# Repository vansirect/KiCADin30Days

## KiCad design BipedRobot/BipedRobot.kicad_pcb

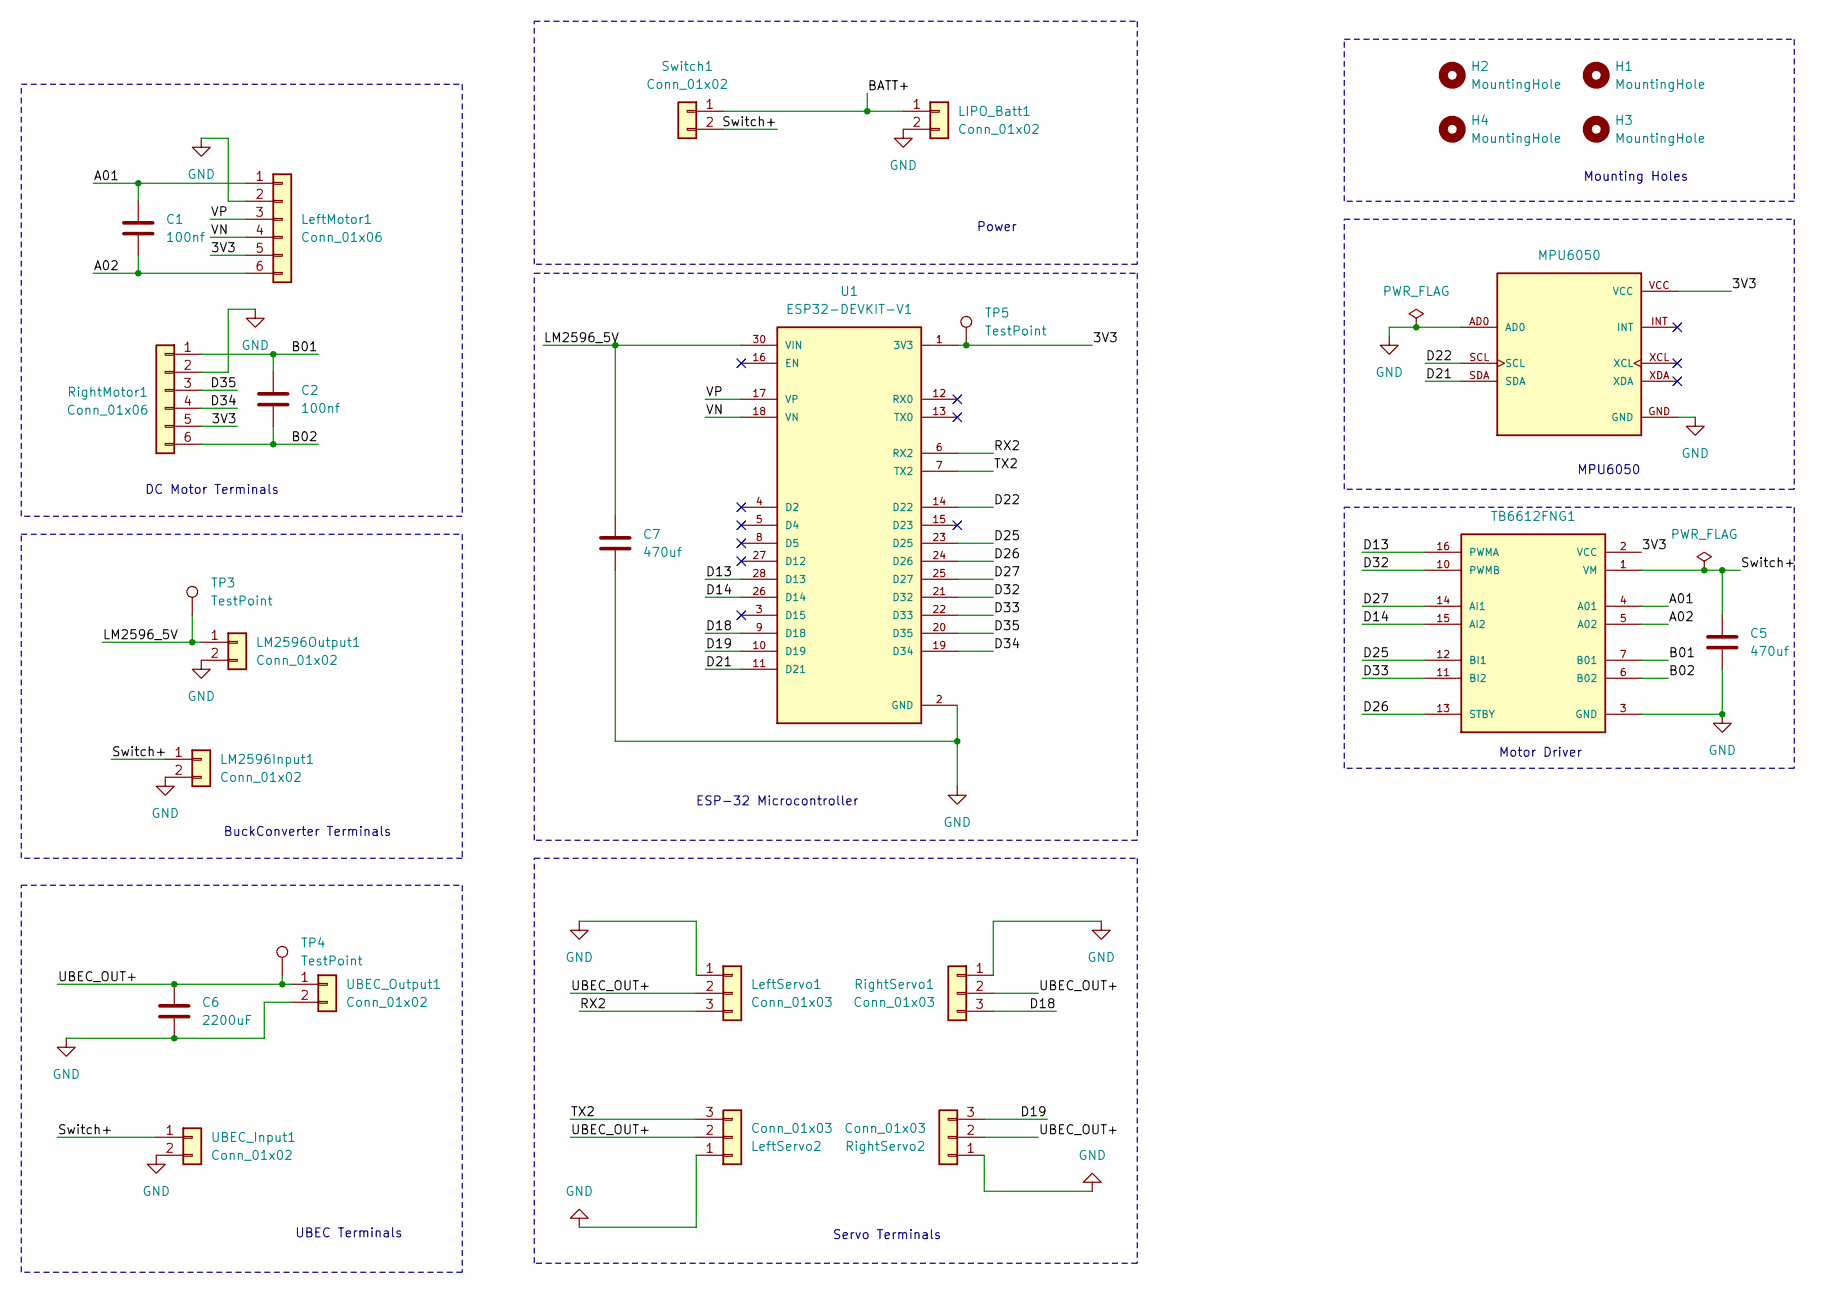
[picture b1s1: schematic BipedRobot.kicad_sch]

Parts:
C1, C2: 100nf; C_Disc_D5.0mm_W2.5mm_P5.00mm
C5, C7: 470uf; CP_Radial_D10.0mm_P5.00mm
C6: 2200uF; CP_Radial_D16.0mm_P7.50mm
H1, H2, H3, H4: MountingHole; MountingHole_3.2mm_M3
LIPO_Batt1: Conn_01x02; AMASS_XT30UPB-M_1x02_P5.0mm_Vertical
LM2596Input1, LM2596Output1: Conn_01x02; SolderWire-0.5sqmm_1x02_P4.6mm_D0.9mm_OD2.1mm
LeftMotor1: Conn_01x06; JST_XH_B6B-XH-A_1x06_P2.50mm_Vertical
LeftServo1, LeftServo2: Conn_01x03; PinHeader_1x03_P2.54mm_Vertical
MPU6050: MPU6050; MODULE_OC09600; PARTREV NA
RightMotor1: Conn_01x06; JST_XH_B6B-XH-A_1x06_P2.50mm_Vertical
RightServo1, RightServo2: Conn_01x03; PinHeader_1x03_P2.54mm_Vertical
Switch1: Conn_01x02; SolderWire-0.5sqmm_1x02_P4.6mm_D0.9mm_OD2.1mm
TB6612FNG1: ROB-14450; MODULE_ROB-14450; PARTREV 11-13-17
TP3, TP4, TP5: TestPoint; TestPoint_Pad_D2.0mm
U1: ESP32-DEVKIT-V1; MODULE_ESP32_DEVKIT_V1; PARTREV N/A
UBEC_Input1: Conn_01x02; SolderWire-1sqmm_1x02_P5.4mm_D1.4mm_OD2.7mm
UBEC_Output1: Conn_01x02; SolderWire-1sqmm_1x02_P5.4mm_D1.4mm_OD2.7mm

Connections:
/3V3: LeftMotor1.5, MPU6050.VCC, RightMotor1.5, TB6612FNG1.2 (VCC), TP5.1 (1_1), U1.1 (3V3); also elsewhere on the board
/A01: C1.1, LeftMotor1.1, TB6612FNG1.4 (A01)
/A02: C1.2, LeftMotor1.6, TB6612FNG1.5 (A02)
/B01: C2.1, RightMotor1.1, TB6612FNG1.7 (B01)
/B02: C2.2, RightMotor1.6, TB6612FNG1.6 (B02)
/BATT+: LIPO_Batt1.1, Switch1.1
/D13: TB6612FNG1.16 (PWMA), U1.28 (D13); also elsewhere on the board
/D14: TB6612FNG1.15 (AI2), U1.26 (D14); also elsewhere on the board
/D18: RightServo1.3, U1.9 (D18); also elsewhere on the board
/D19: RightServo2.3, U1.10 (D19); also elsewhere on the board
/D21: MPU6050.SDA, U1.11 (D21); also elsewhere on the board
/D22: MPU6050.SCL, U1.14 (D22); also elsewhere on the board
/D25: TB6612FNG1.12 (BI1), U1.23 (D25); also elsewhere on the board
/D26: TB6612FNG1.13 (STBY), U1.24 (D26); also elsewhere on the board
/D27: TB6612FNG1.14 (AI1), U1.25 (D27); also elsewhere on the board
/D32: TB6612FNG1.10 (PWMB), U1.21 (D32); also elsewhere on the board
/D33: TB6612FNG1.11 (BI2), U1.22 (D33); also elsewhere on the board
/D34: RightMotor1.4, U1.19 (D34); also elsewhere on the board
/D35: RightMotor1.3, U1.20 (D35); also elsewhere on the board
/LM2596_5V: C7.1, LM2596Output1.1, TP3.1 (1_1), U1.30 (VIN); also elsewhere on the board
/RX2: LeftServo1.3, U1.6 (RX2); also elsewhere on the board
/Switch+: C5.1, LM2596Input1.1, Switch1.2, TB6612FNG1.1 (VM), UBEC_Input1.1
/TX2: LeftServo2.3, U1.7 (TX2); also elsewhere on the board
/UBEC_OUT+: C6.1, LeftServo1.2, LeftServo2.2, RightServo1.2, RightServo2.2, TP4.1 (1_1), UBEC_Output1.1
/VN: LeftMotor1.4, U1.18 (VN); also elsewhere on the board
/VP: LeftMotor1.3, U1.17 (VP); also elsewhere on the board
GND: C5.2, C6.2, C7.2, LIPO_Batt1.2, LM2596Input1.2, LM2596Output1.2, LeftMotor1.2, LeftServo1.1, LeftServo2.1, MPU6050.AD0, MPU6050.GND, RightMotor1.2, RightServo1.1, RightServo2.1, TB6612FNG1.3 (GND), TB6612FNG1.8 (GND), TB6612FNG1.9 (GND), U1.2 (GND), U1.29 (GND), UBEC_Input1.2, UBEC_Output1.2; also elsewhere on the board

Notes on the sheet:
DC Motor Terminals
MPU6050
Mounting Holes
Servo Terminals
Power
ESP-32 Microcontroller
UBEC Terminals
BuckConverter Terminals
Motor Driver

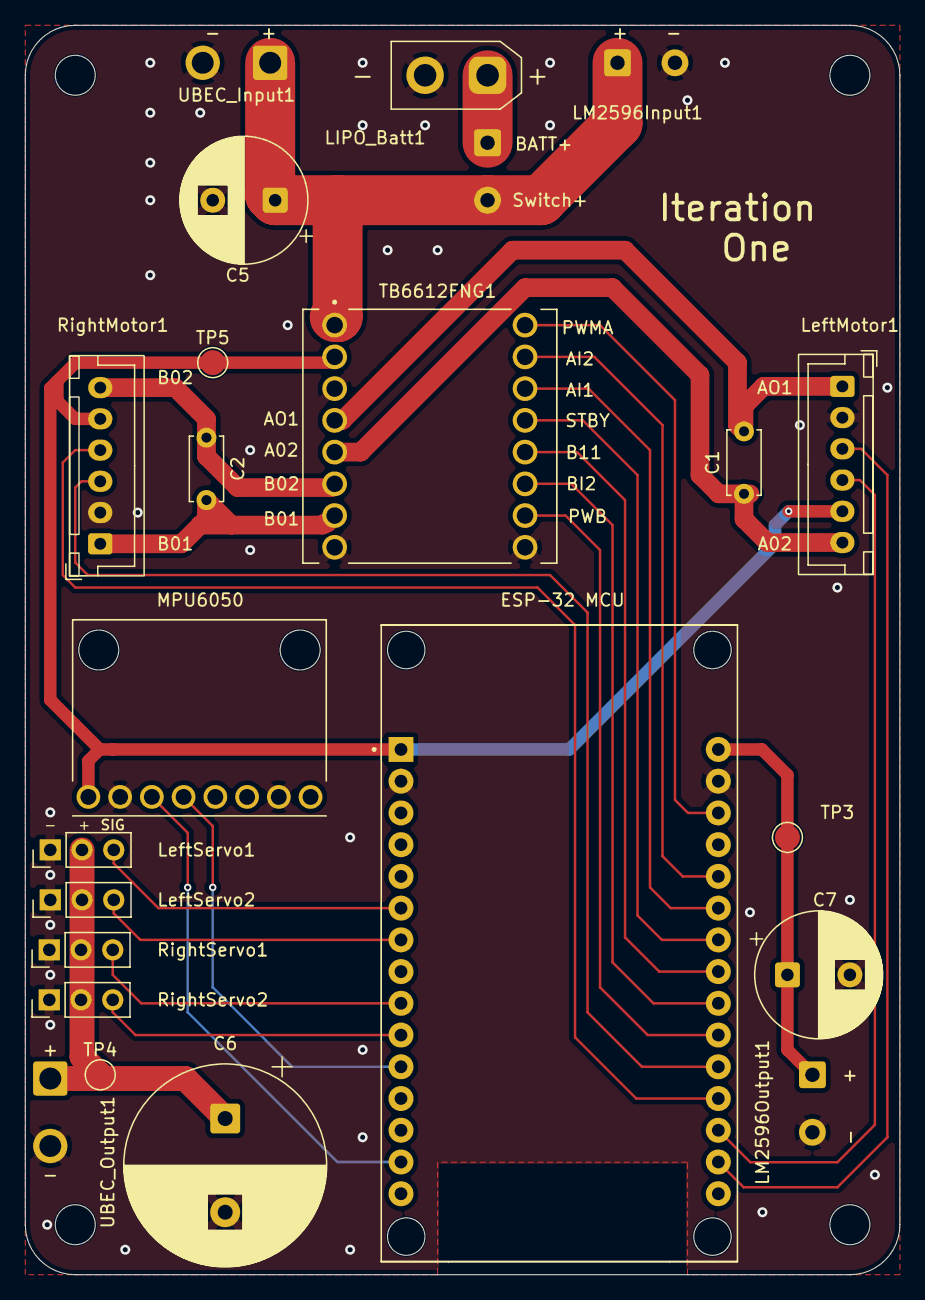
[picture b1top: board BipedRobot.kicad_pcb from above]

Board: 2 copper layers, 70.0 x 100.0 mm, 27 parts (0 on the bottom side), 27 nets.

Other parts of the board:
ESP-32 MCU: ESP32-DEVKIT-V1; MODULE_ESP32_DEVKIT_V1

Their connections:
/3V3: ESP-32 MCU.1 (3V3); also elsewhere on the board
/D13: ESP-32 MCU.28 (D13); also elsewhere on the board
/D14: ESP-32 MCU.26 (D14); also elsewhere on the board
/D18: ESP-32 MCU.9 (D18); also elsewhere on the board
/D19: ESP-32 MCU.10 (D19); also elsewhere on the board
/D21: ESP-32 MCU.11 (D21); also elsewhere on the board
/D22: ESP-32 MCU.14 (D22); also elsewhere on the board
/D25: ESP-32 MCU.23 (D25); also elsewhere on the board
/D26: ESP-32 MCU.24 (D26); also elsewhere on the board
/D27: ESP-32 MCU.25 (D27); also elsewhere on the board
/D32: ESP-32 MCU.21 (D32); also elsewhere on the board
/D33: ESP-32 MCU.22 (D33); also elsewhere on the board
/D34: ESP-32 MCU.19 (D34); also elsewhere on the board
/D35: ESP-32 MCU.20 (D35); also elsewhere on the board
/LM2596_5V: ESP-32 MCU.30 (VIN); also elsewhere on the board
/RX2: ESP-32 MCU.6 (RX2); also elsewhere on the board
/TX2: ESP-32 MCU.7 (TX2); also elsewhere on the board
/VN: ESP-32 MCU.18 (VN); also elsewhere on the board
/VP: ESP-32 MCU.17 (VP); also elsewhere on the board
GND: ESP-32 MCU.2 (GND), ESP-32 MCU.29 (GND); also elsewhere on the board

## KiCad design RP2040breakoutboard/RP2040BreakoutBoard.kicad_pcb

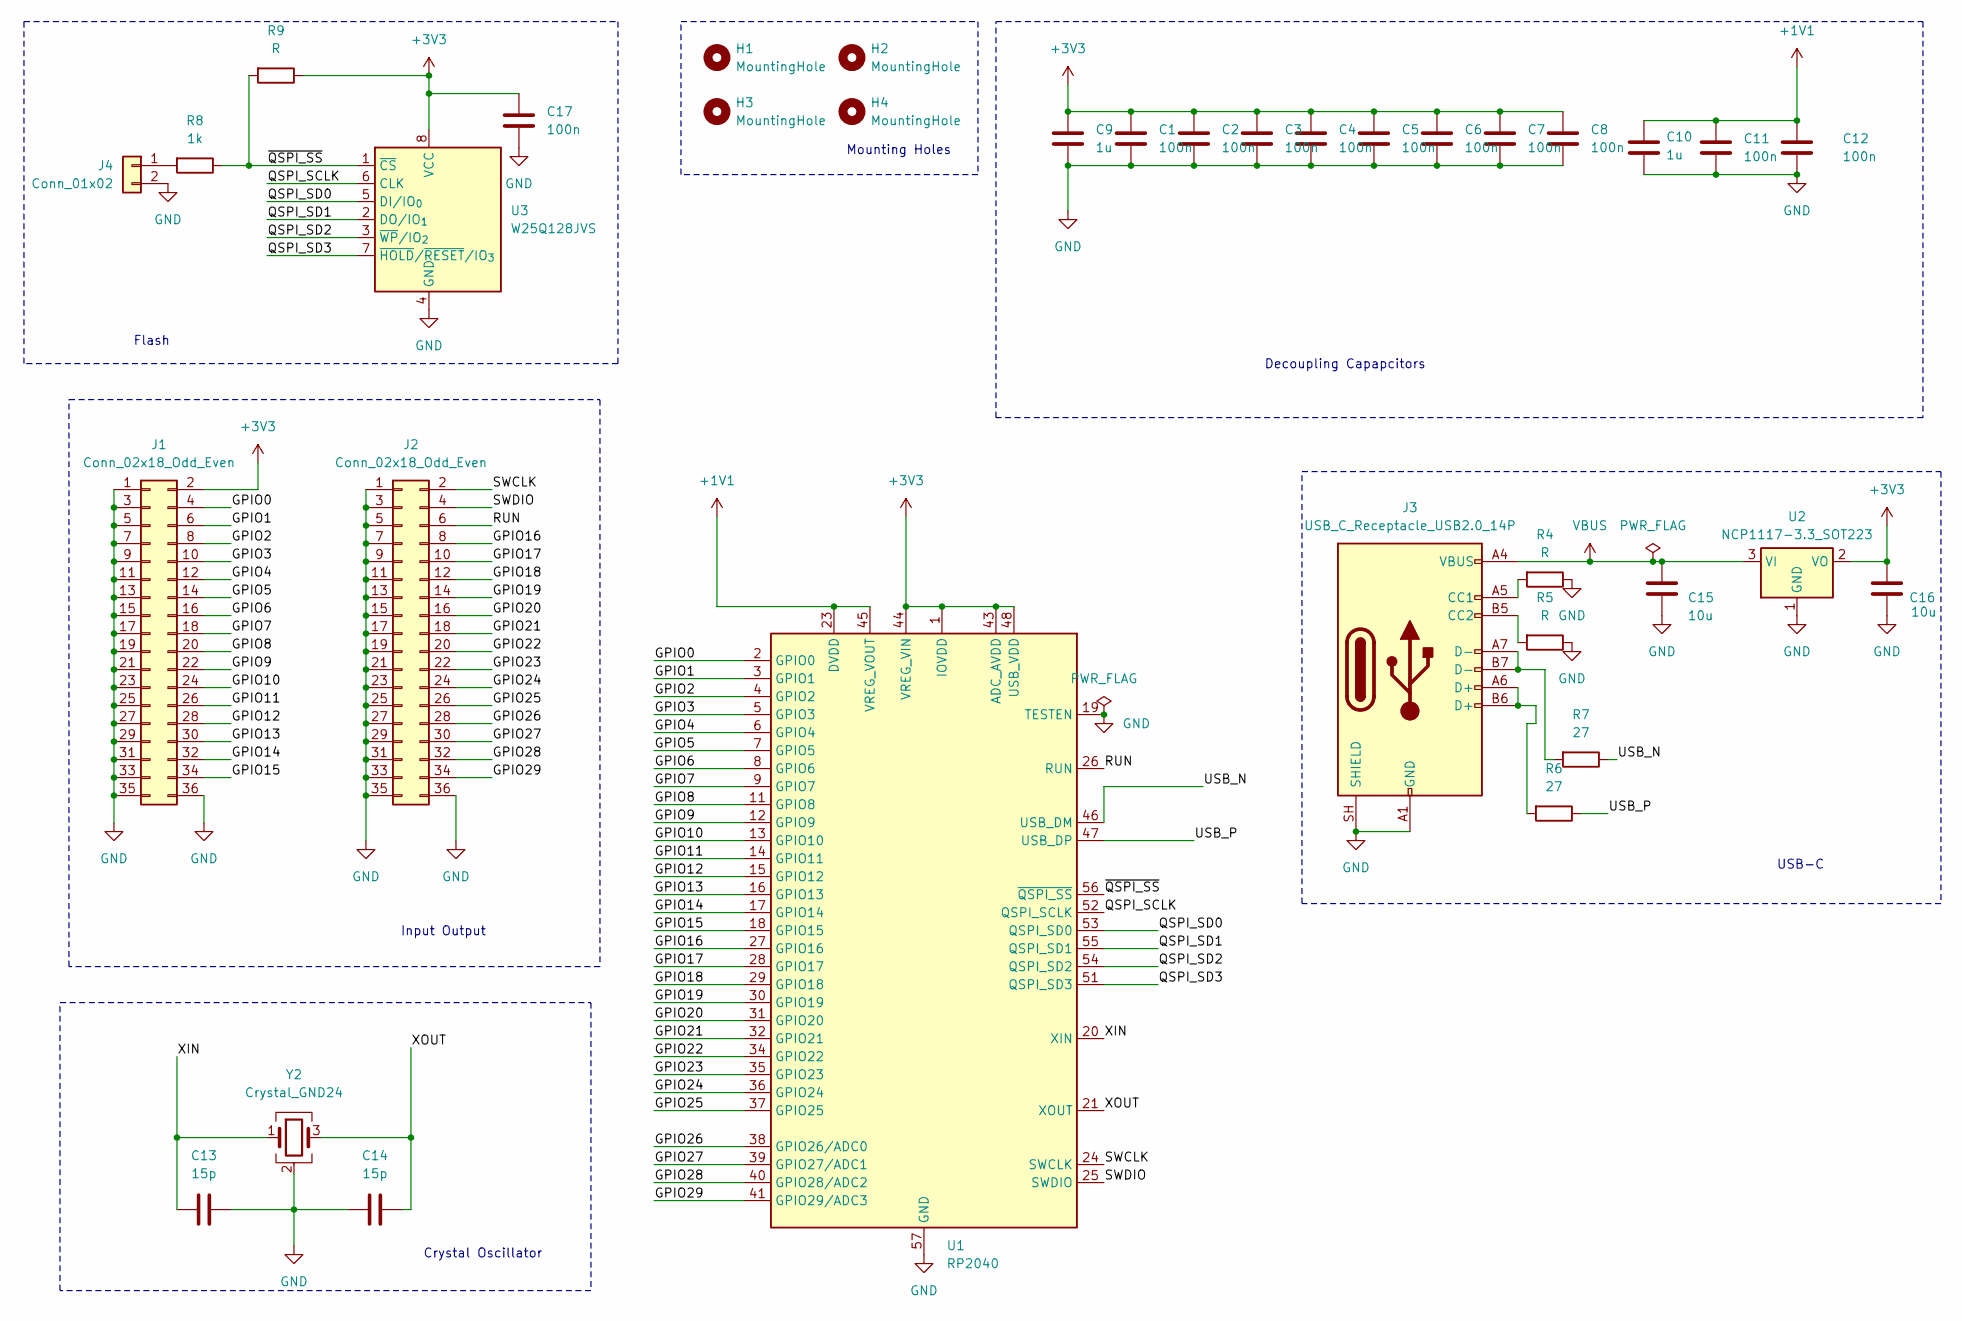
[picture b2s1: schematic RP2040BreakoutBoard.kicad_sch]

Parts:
C1, C2, C3, C4, C5, C6, C7, C8, C11, C12, C17: 100n; C_0603_1608Metric
C9, C10: 1u; C_0603_1608Metric
C13, C14: 15p; C_0603_1608Metric
C15, C16: 10u; C_0805_2012Metric
H1, H2, H3, H4: MountingHole; MountingHole_3.2mm_M3
J1, J2: Conn_02x18_Odd_Even; PinHeader_2x18_P2.54mm_Vertical
J3: USB_C_Receptacle_USB2.0_14P; USB_C_Receptacle_GCT_USB4105-xx-A_16P_TopMnt_Horizontal
J4: Conn_01x02; PinHeader_1x02_P2.54mm_Vertical
R4, R5, R9: R; R_0603_1608Metric
R6, R7: 27; R_0603_1608Metric
R8: 1k; R_0603_1608Metric
U1: RP2040; QFN-56-1EP_7x7mm_P0.4mm_EP3.2x3.2mm
U2: NCP1117-3.3_SOT223; SOT-223-3_TabPin2
U3: W25Q128JVS; SOIC-8_5.3x5.3mm_P1.27mm
Y2: Crystal_GND24; Crystal_SMD_3225-4Pin_3.2x2.5mm

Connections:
+1V1: C10.1, C11.1, C12.1, U1.23 (DVDD), U1.45 (VREG_VOUT), U1.50 (DVDD)
+3V3: C1.1, C2.1, C3.1, C4.1, C5.1, C6.1, C7.1, C8.1, C9.1, C16.2, C17.1, J1.2, R9.1, U1.1 (IOVDD), U1.10 (IOVDD), U1.22 (IOVDD), U1.33 (IOVDD), U1.42 (IOVDD), U1.43 (ADC_AVDD), U1.44 (VREG_VIN), U1.48 (USB_VDD), U1.49 (IOVDD), U2.2 (VO), U3.8 (VCC)
/GPIO0: J1.4, U1.2 (GPIO0)
/GPIO1: J1.6, U1.3 (GPIO1)
/GPIO2: J1.8, U1.4 (GPIO2)
/GPIO3: J1.10, U1.5 (GPIO3)
/GPIO4: J1.12, U1.6 (GPIO4)
/GPIO5: J1.14, U1.7 (GPIO5)
/GPIO6: J1.16, U1.8 (GPIO6)
/GPIO7: J1.18, U1.9 (GPIO7)
/GPIO8: J1.20, U1.11 (GPIO8)
/GPIO9: J1.22, U1.12 (GPIO9)
/GPIO10: J1.24, U1.13 (GPIO10)
/GPIO11: J1.26, U1.14 (GPIO11)
/GPIO12: J1.28, U1.15 (GPIO12)
/GPIO13: J1.30, U1.16 (GPIO13)
/GPIO14: J1.32, U1.17 (GPIO14)
/GPIO15: J1.34, U1.18 (GPIO15)
/GPIO16: J2.8, U1.27 (GPIO16)
/GPIO17: J2.10, U1.28 (GPIO17)
/GPIO18: J2.12, U1.29 (GPIO18)
/GPIO19: J2.14, U1.30 (GPIO19)
/GPIO20: J2.16, U1.31 (GPIO20)
/GPIO21: J2.18, U1.32 (GPIO21)
/GPIO22: J2.20, U1.34 (GPIO22)
/GPIO23: J2.22, U1.35 (GPIO23)
/GPIO24: J2.24, U1.36 (GPIO24)
/GPIO25: J2.26, U1.37 (GPIO25)
/GPIO26: J2.28, U1.38 (GPIO26/ADC0)
/GPIO27: J2.30, U1.39 (GPIO27/ADC1)
/GPIO28: J2.32, U1.40 (GPIO28/ADC2)
/GPIO29: J2.34, U1.41 (GPIO29/ADC3)
/QSPI_SCLK: U1.52 (QSPI_SCLK), U3.6 (CLK)
/QSPI_SD0: U1.53 (QSPI_SD0), U3.5 (DI/IO_{0})
/QSPI_SD1: U1.55 (QSPI_SD1), U3.2 (DO/IO_{1})
/QSPI_SD2: U1.54 (QSPI_SD2), U3.3 (~WP/IO_{2})
/QSPI_SD3: U1.51 (QSPI_SD3), U3.7 (~HOLD/~RESET/IO_{3})
/RUN: J2.6, U1.26 (RUN)
/SWCLK: J2.2, U1.24 (SWCLK)
/SWDIO: J2.4, U1.25 (SWDIO)
/USB_N: R7.1, U1.46 (USB_DM)
/USB_P: R6.1, U1.47 (USB_DP)
/XIN: C13.2, U1.20 (XIN), Y2.1
/XOUT: C14.1, U1.21 (XOUT), Y2.3
/~QSPI_SS: R8.1, R9.2, U1.56 (~QSPI_SS), U3.1 (~CS)
GND: C1.2, C2.2, C3.2, C4.2, C5.2, C6.2, C7.2, C8.2, C9.2, C10.2, C11.2, C12.2, C13.1, C14.2, C15.1, C16.1, C17.2, J1.1, J1.3, J1.5, J1.7, J1.9, J1.11, J1.13, J1.15, J1.17, J1.19, J1.21, J1.23, J1.25, J1.27, J1.29, J1.31, J1.33, J1.35, J1.36, J2.1, J2.3, J2.5, J2.7, J2.9, J2.11, J2.13, J2.15, J2.17, J2.19, J2.21, J2.23, J2.25, J2.27, J2.29, J2.31, J2.33, J2.35, J2.36, J3.A1 (GND), J3.A12 (GND), J3.B1 (GND), J3.B12 (GND), J3.SH (SHIELD), J4.2, R4.1, R5.1, U1.19 (TESTEN), U1.57 (GND), U2.1 (GND), U3.4 (GND), Y2.2 (G), Y2.4 (G)
unnamed: J3.A5 (CC1), R4.2
unnamed: J3.B5 (CC2), R5.2
unnamed: J3.A6 (D+), J3.B6 (D+), R6.2
unnamed: J3.A7 (D-), J3.B7 (D-), R7.2
unnamed: J4.1, R8.2
VBUS: C15.2, J3.A4 (VBUS), J3.A9 (VBUS), J3.B4 (VBUS), J3.B9 (VBUS), U2.3 (VI)

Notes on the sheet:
USB-C
Crystal Oscillator
Mounting Holes
Flash
Decoupling Capapcitors
Input Output

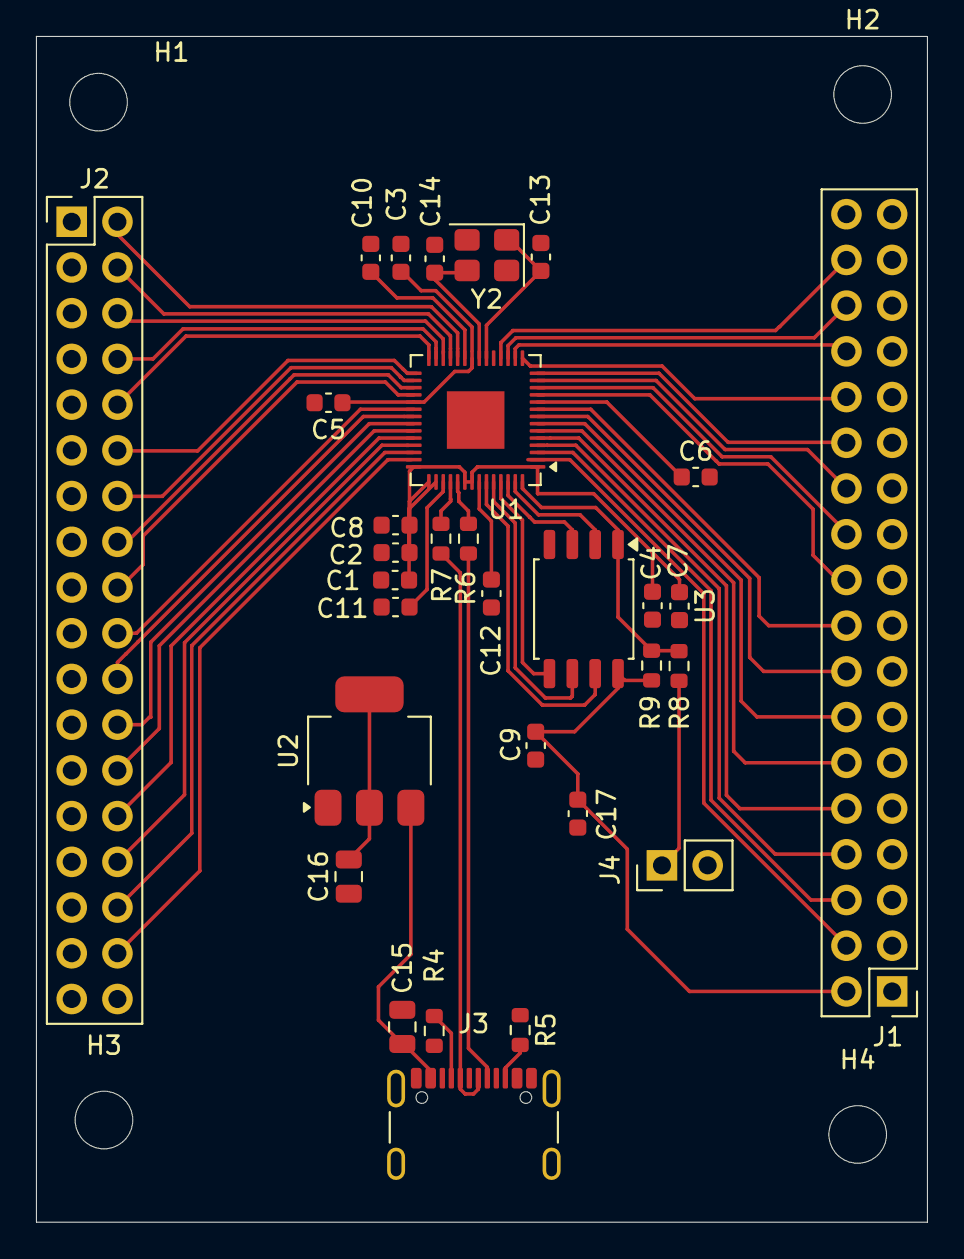
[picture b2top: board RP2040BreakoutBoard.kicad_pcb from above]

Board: 2 copper layers, 49.5 x 65.9 mm, 35 parts (0 on the bottom side), 52 nets.

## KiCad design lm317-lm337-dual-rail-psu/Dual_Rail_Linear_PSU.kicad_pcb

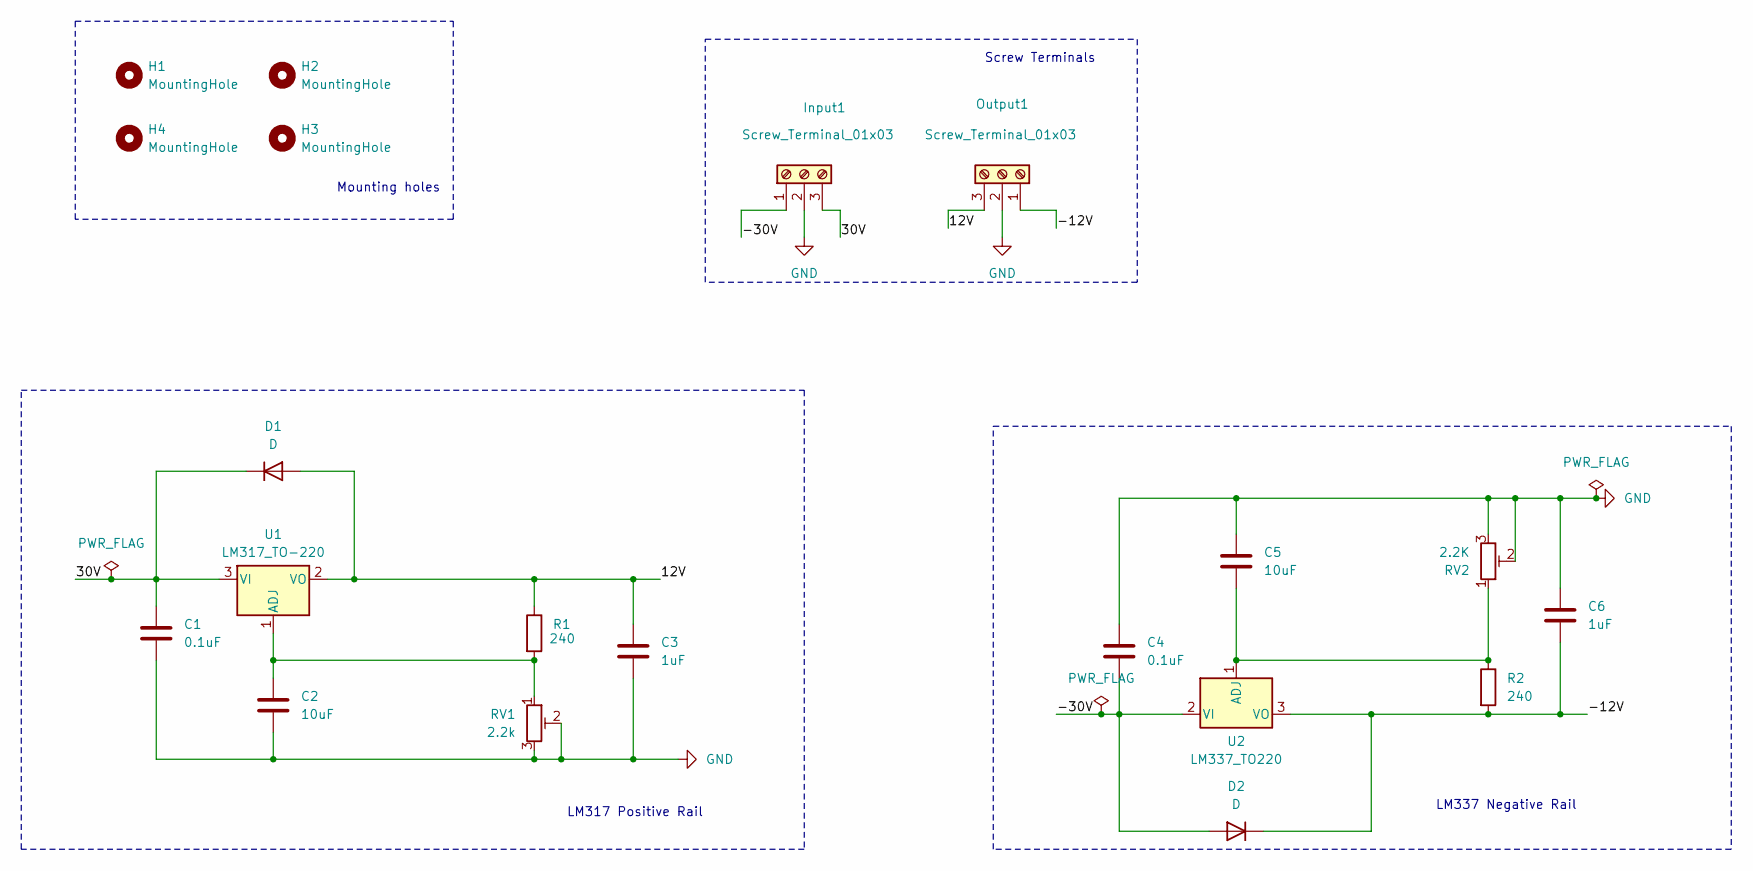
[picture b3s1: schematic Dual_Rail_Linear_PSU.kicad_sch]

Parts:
C1, C4: 0.1uF; C_Disc_D5.0mm_W2.5mm_P5.00mm
C2, C5: 10uF; CP_Radial_D5.0mm_P2.00mm
C3, C6: 1uF; CP_Radial_D5.0mm_P2.00mm
D1, D2: D; D_DO-41_SOD81_P10.16mm_Horizontal
H1, H2, H3, H4: MountingHole; MountingHole_3.2mm_M3
Input1: Screw_Terminal_01x03; TerminalBlock_Phoenix_MKDS-1,5-3_1x03_P5.00mm_Horizontal
Output1: Screw_Terminal_01x03; TerminalBlock_Phoenix_MKDS-1,5-3_1x03_P5.00mm_Horizontal
R1, R2: 240; R_Axial_DIN0207_L6.3mm_D2.5mm_P10.16mm_Horizontal
RV1: 2.2k; Potentiometer_Bourns_3296W_Vertical
RV2: 2.2K; Potentiometer_Bourns_3296W_Vertical
U1: LM317_TO-220; TO-220-3_Vertical
U2: LM337_TO220; TO-220-3_Vertical

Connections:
/12V: C3.1, D1.2 (A), Output1.3, R1.1, U1.2 (VO)
/30V: C1.1, D1.1 (K), Input1.3, U1.3 (VI)
/-12V: C6.2, D2.1 (K), Output1.1, R2.2, U2.3 (VO)
/-30V: C4.2, D2.2 (A), Input1.1, U2.2 (VI)
GND: C1.2, C2.2, C3.2, C4.1, C5.1, C6.1, Input1.2, Output1.2, RV1.2, RV1.3, RV2.2, RV2.3
unnamed: C2.1, R1.2, RV1.1, U1.1 (ADJ)
unnamed: C5.2, R2.1, RV2.1, U2.1 (ADJ)

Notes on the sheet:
Screw Terminals
LM337 Negative Rail
LM317 Positive Rail
Mounting holes

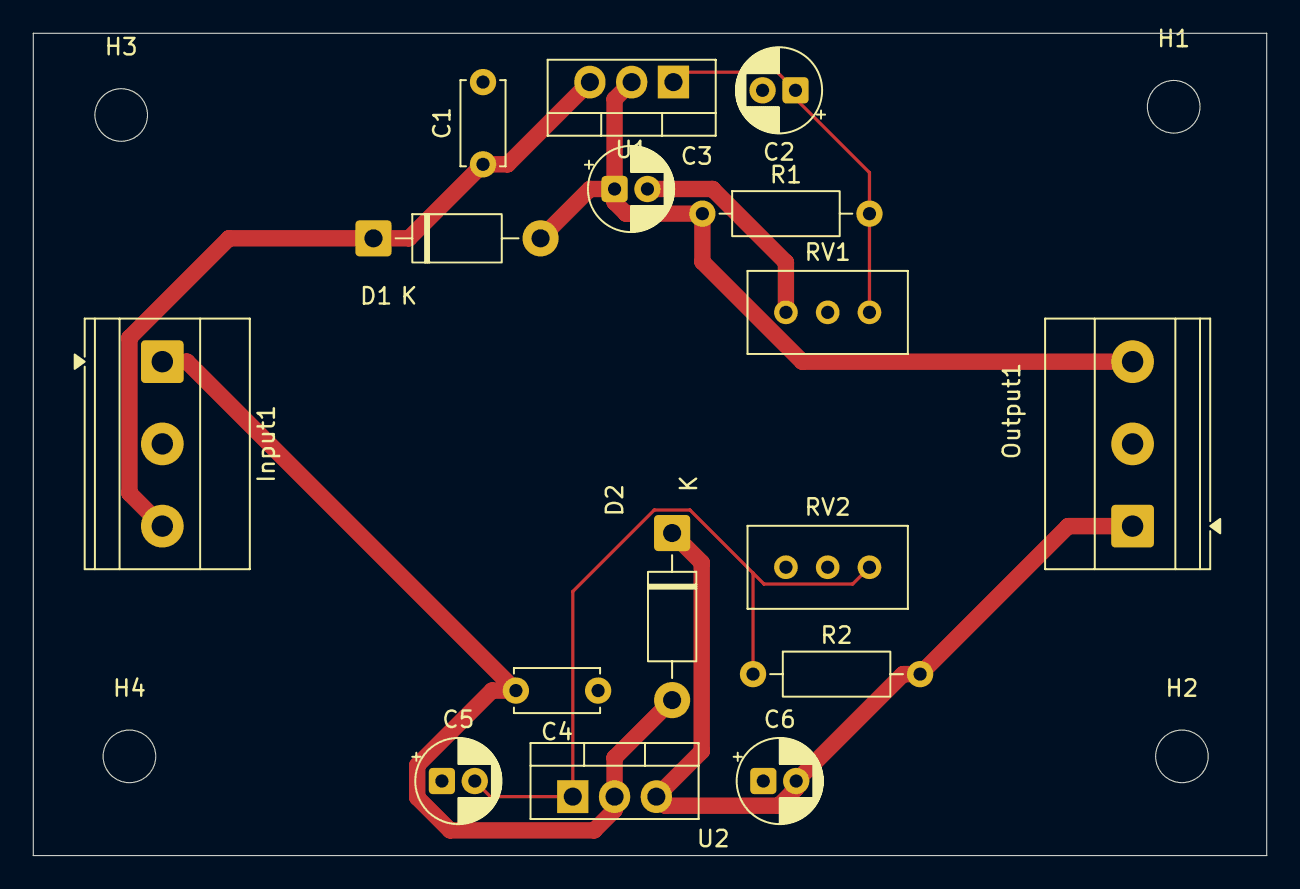
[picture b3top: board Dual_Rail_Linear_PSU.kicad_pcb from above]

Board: 2 copper layers, 75.0 x 50.0 mm, 20 parts (0 on the bottom side), 7 nets.
